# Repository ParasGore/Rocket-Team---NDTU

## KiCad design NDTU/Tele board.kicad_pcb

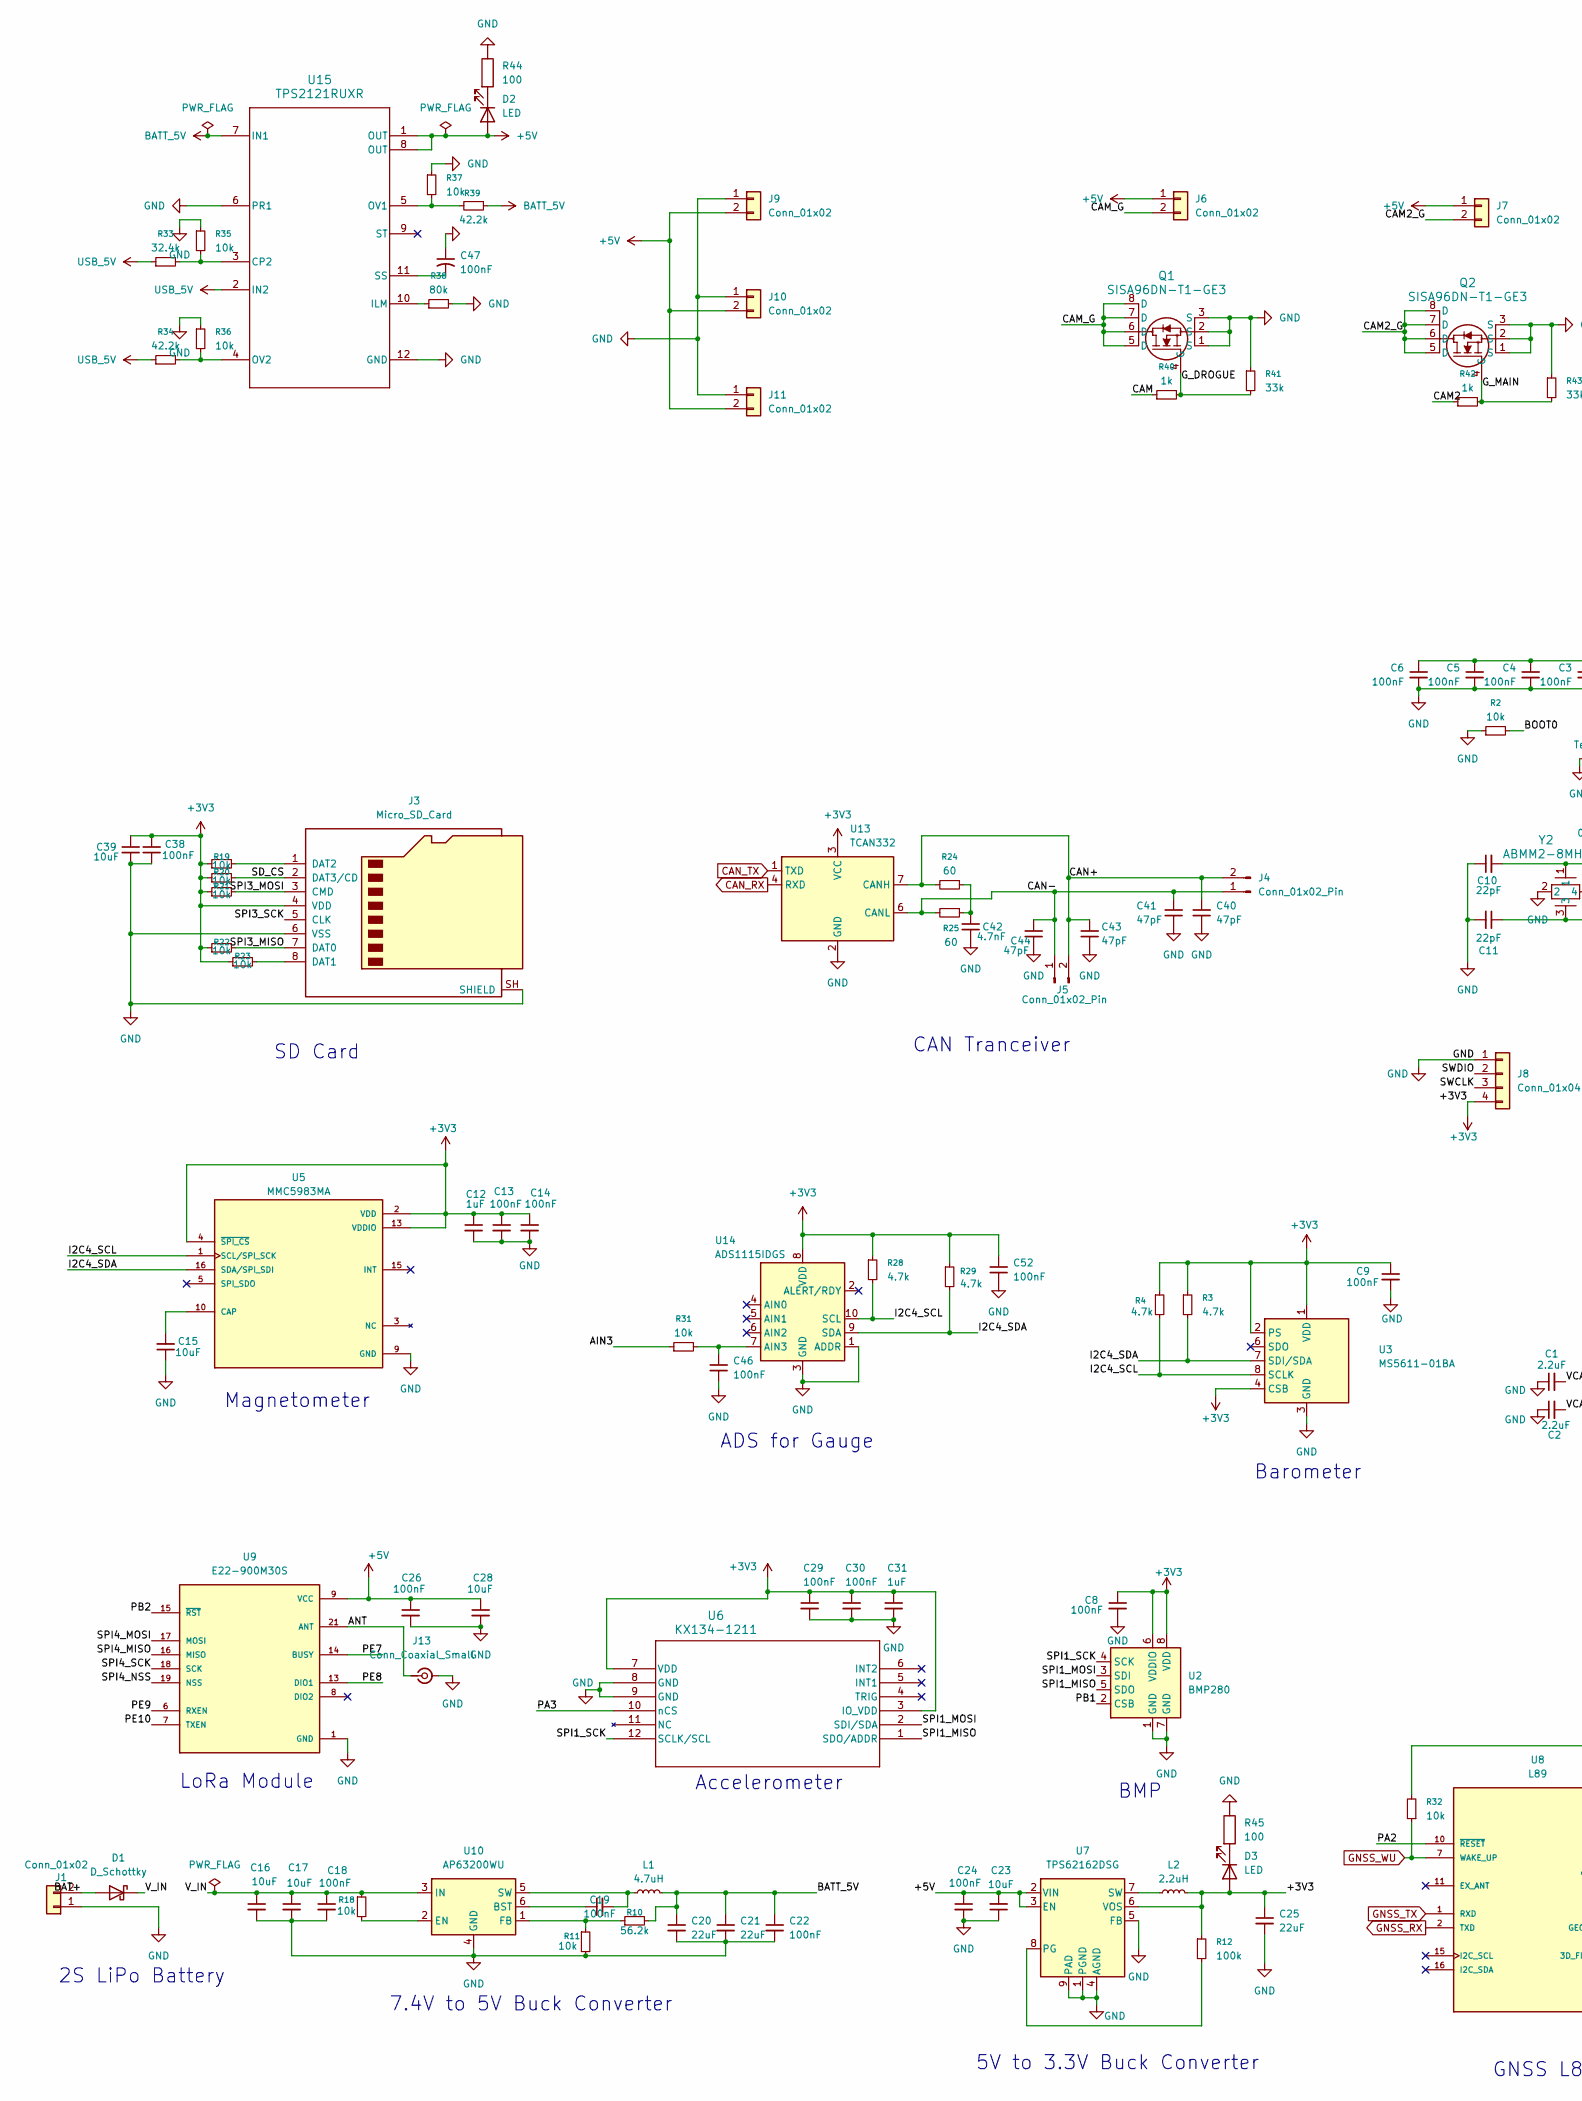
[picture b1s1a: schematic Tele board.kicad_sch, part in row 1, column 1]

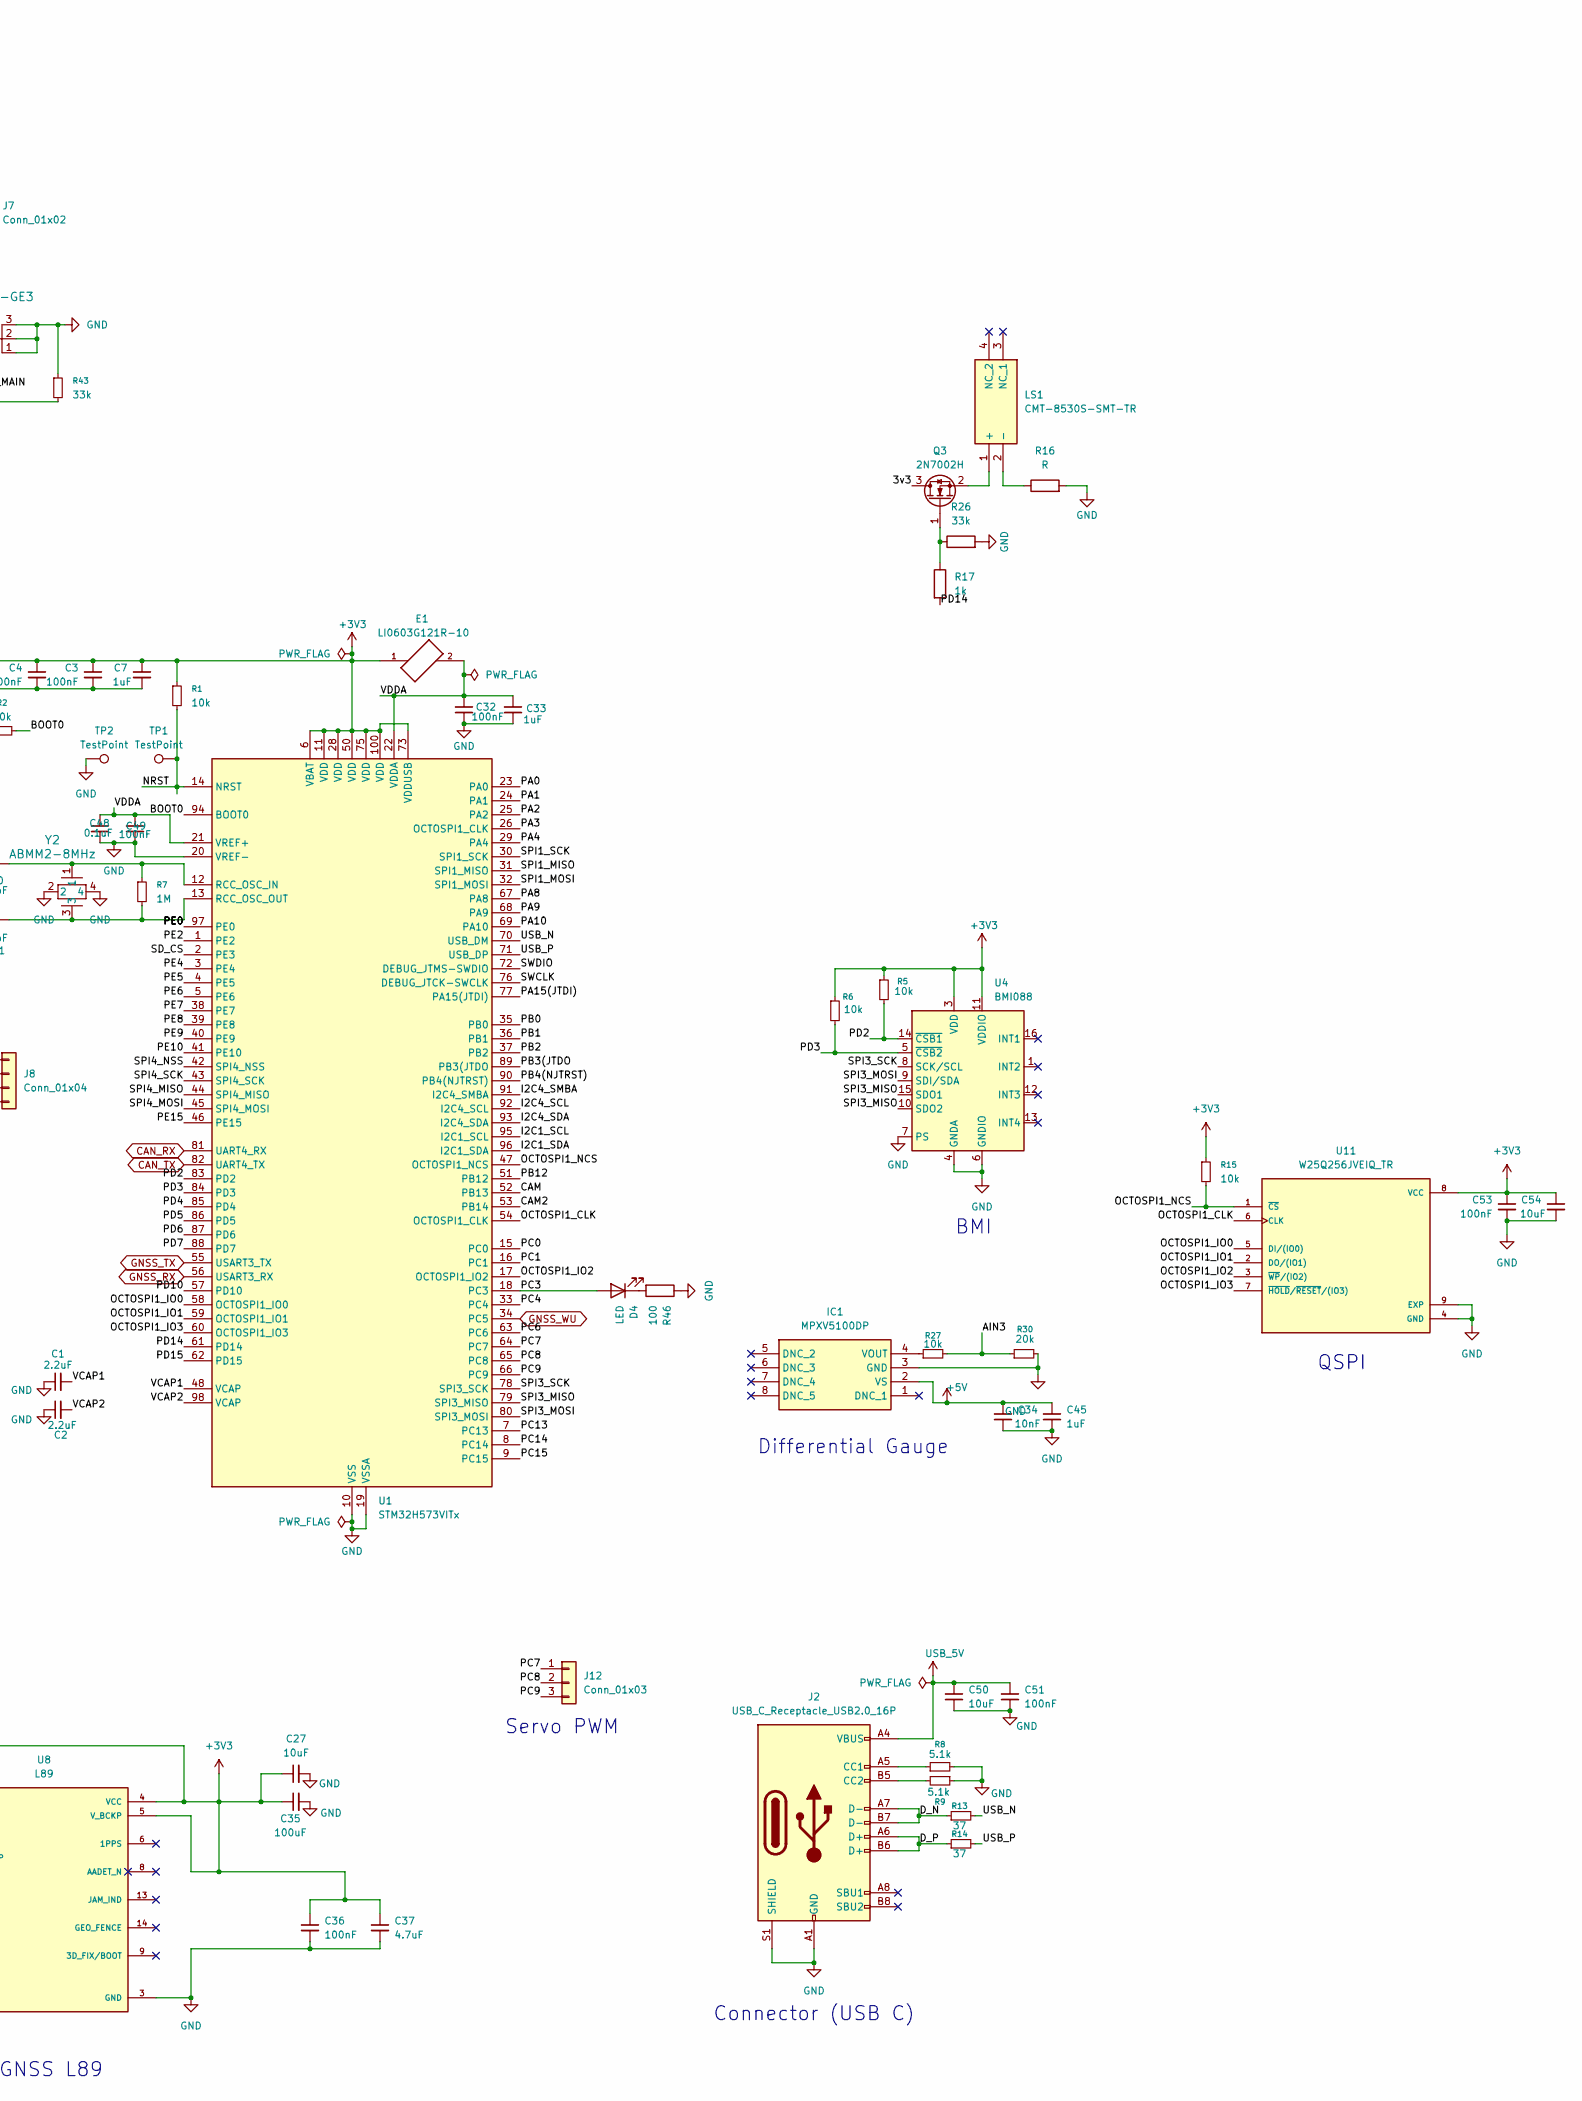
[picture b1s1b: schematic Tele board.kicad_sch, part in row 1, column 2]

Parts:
C1, C2: 2.2uF; C_0603_1608Metric
C3, C4, C5, C6, C8, C9, C13, C14, C18, C19, C22, C24, C26, C29, C30, C32, C36, C38, C46, C47, C49, C51, C52, C53: 100nF; C_0603_1608Metric
C7, C12, C31, C33, C45: 1uF; C_0603_1608Metric
C10, C11: 22pF; C_0603_1608Metric
C15, C16, C17, C23, C27, C28, C39, C50, C54: 10uF; C_0603_1608Metric
C20, C21, C25: 22uF; C_0603_1608Metric
C34: 10nF; C_0603_1608Metric
C35: 100uF; C_0603_1608Metric
C37: 4.7uF; C_0603_1608Metric
C40, C41, C43, C44: 47pF; C_0603_1608Metric
C42: 4.7nF; C_0603_1608Metric
C48: 0.1uF; C_0603_1608Metric
D1: D_Schottky; D_SOD-128
D2, D3, D4: LED; LED_0603_1608Metric
E1: LI0603G121R-10; IND_LI0603G121R-10_LRD-M; PARTREV C
IC1: MPXV5100DP; Manufacturer_Part_Number MPXV5100DP
J1: Conn_01x02; AMASS_XT30U-M_1x02_P5.0mm_Vertical
J2: USB_C_Receptacle_USB2.0_16P; USB_C_Receptacle_GCT_USB4105-xx-A_16P_TopMnt_Horizontal
J3: Micro_SD_Card; microSD_HC_Hirose_DM3AT-SF-PEJM5
J4, J5: Conn_01x02_Pin; JST_EH_B2B-EH-A_1x02_P2.50mm_Vertical
J6, J7, J9, J10, J11: Conn_01x02; JST_EH_B2B-EH-A_1x02_P2.50mm_Vertical
J8: Conn_01x04; JST_EH_B4B-EH-A_1x04_P2.50mm_Vertical
J12: Conn_01x03; AMASS_MR30PW-M_1x03_P3.50mm_Horizontal
J13: Conn_Coaxial_Small; SMA_Samtec_SMA-J-P-H-ST-EM1_EdgeMount
L1: 4.7uH; L_Coilcraft_XAL4020-XXX
L2: 2.2uH; L_Coilcraft_XAL4020-XXX
LS1: CMT-8530S-SMT-TR; CMT8530SSMTTR; Manufacturer_Part_Number CMT-8530S-SMT-TR; Mouser Part Number 490-CMT-8530S-SMT-TR
Q1, Q2: SISA96DN-T1-GE3; SIS862DNT1GE3
Q3: 2N7002H; SOT-23
R1, R2, R5, R6, R11, R15, R18, R19, R20, R21, R22, R23, R27, R31, R32, R35, R36, R37: 10k; R_0603_1608Metric
R3, R4, R28, R29: 4.7k; R_0603_1608Metric
R7: 1M; R_0603_1608Metric
R8, R9: 5.1k; R_0603_1608Metric
R10: 56.2k; R_0603_1608Metric
R12: 100k; R_0603_1608Metric
R13, R14: 37; R_0603_1608Metric
R16: R; R_0603_1608Metric
R17, R40, R42: 1k; R_0603_1608Metric
R24, R25: 60; R_0603_1608Metric
R26, R41, R43: 33k; R_0603_1608Metric
R30: 20k; R_0603_1608Metric
R33: 32.4k; R_0603_1608Metric
R34, R39: 42.2k; R_0603_1608Metric
R38: 80k; R_0603_1608Metric
R44, R45, R46: 100; R_0603_1608Metric
TP1, TP2: TestPoint; TestPoint_Pad_2.0x2.0mm
U1: STM32H573VITx; LQFP-100_14x14mm_P0.5mm
U2: BMP280; Bosch_LGA-8_2x2.5mm_P0.65mm_ClockwisePinNumbering
U3: MS5611-01BA; LGA-8_3x5mm_P1.25mm
U4: BMI088; Bosch_LGA-16_4.5x3mm_P0.5mm_LayoutBorder7x1y_ClockwisePinNu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
U5: MMC5983MA; PQFN50P300X300X100-16N; PARTREV A
U6: KX134-1211; LGA12_2X2X0P9_ROM-M
U7: TPS62162DSG; Texas_DSG0008A_WSON-8-1EP_2x2mm_P0.5mm_EP0.9x1.6mm_ThermalV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
U8: L89; XCVR_L89; PARTREV 1.1
U9: E22-900M30S; XCVR_E22-900M30S; PARTREV 1.2
U10: AP63200WU; TSOT-23-6
U11: W25Q256JVEIQ_TR; W25Q256JVEIQ; MPN W25Q256JVEIQ TR
U13: TCAN332; SOIC-8_3.9x4.9mm_P1.27mm
U14: ADS1115IDGS; TSSOP-10_3x3mm_P0.5mm
U15: TPS2121RUXR; IC_TPS2121RUXR
Y2: ABMM2-8MHz; CRYSTAL_ABMM2_ABR

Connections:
+3V3: C3.1, C4.1, C5.1, C6.1, C7.1, C8.1, C9.1, C12.1, C13.1, C14.1, C25.1, C27.1, C29.1, C30.1, C31.1, C35.1, C36.1, C37.1, C38.1, C39.1, C52.1, C53.1, C54.1, D3.2 (A), E1.1, J3.4 (VDD), J8.4, L2.2, R1.1, R3.1, R4.1, R5.1, R6.1, R12.1, R15.1, R19.1, R20.1, R21.1, R22.1, R23.1, R28.1, R29.1, R32.2, U1.6 (VBAT), U1.11 (VDD), U1.28 (VDD), U1.50 (VDD), U1.73 (VDDUSB), U1.75 (VDD), U1.100 (VDD), U2.6 (VDDIO), U2.8 (VDD), U3.1 (VDD), U3.2 (PS), U3.4 (CSB), U3.5 (CSB), U4.3 (VDD), U4.11 (VDDIO), U5.2 (VDD), U5.4 (~SPI_CS), U5.13 (VDDIO), U6.3 (IO_VDD), U6.7 (VDD), U7.6 (VOS), U8.4 (VCC), U8.5 (V_BCKP), U11.8 (VCC), U13.3 (VCC), U14.8 (VDD)
+5V: C23.2, C24.1, C26.1, C28.1, C34.1, C45.1, D2.2 (A), IC1.2 (VS), J6.1, J7.1, J9.2, J10.2, J11.2, U7.2 (VIN), U7.3 (EN), U9.9 (VCC), U9.10 (VCC), U15.1 (OUT), U15.8 (OUT)
/3v3: Q3.3 (D)
/AIN3: R27.2, R30.1, R31.1
/ANT: J13.1 (In), U9.21 (ANT)
/BAT+: D1.2 (A), J1.2
/BOOT0: R2.2, U1.94 (BOOT0)
/CAM: R40.1, U1.52 (PB13)
/CAM2: R42.1, U1.53 (PB14)
/CAM2_G: J7.2, Q2.5 (D), Q2.6 (D), Q2.7 (D), Q2.8 (D)
/CAM_G: J6.2, Q1.5 (D), Q1.6 (D), Q1.7 (D), Q1.8 (D)
/CAN+: C40.1, C43.1, J4.2, J5.2, R24.2, U13.7 (CANH); also elsewhere on the board
/CAN-: C41.1, C44.1, J4.1, J5.1, R25.2, U13.6 (CANL); also elsewhere on the board
/D_N: J2.A7 (D-), J2.B7 (D-), R13.1
/D_P: J2.A6 (D+), J2.B6 (D+), R14.1
/G_DROGUE: Q1.4 (G), R40.2, R41.2
/G_MAIN: Q2.4 (G), R42.2, R43.2
/I2C1_SCL: U1.95 (I2C1_SCL)
/I2C1_SDA: U1.96 (I2C1_SDA)
/I2C4_SCL: R4.2, R28.2, U1.92 (I2C4_SCL), U3.8 (SCLK), U5.1 (SCL/SPI_SCK), U14.10 (SCL)
/I2C4_SDA: R3.2, R29.2, U1.93 (I2C4_SDA), U3.7 (SDI/SDA), U5.16 (SDA/SPI_SDI), U14.9 (SDA)
/I2C4_SMBA: U1.91 (I2C4_SMBA)
/NRST: R1.2, TP1.1 (1_1), U1.14 (NRST)
/OCTOSPI1_CLK: U1.54 (OCTOSPI1_CLK), U11.6 (CLK)
/OCTOSPI1_IO0: U1.58 (OCTOSPI1_IO0), U11.5 (DI/(IO0))
/OCTOSPI1_IO1: U1.59 (OCTOSPI1_IO1), U11.2 (DO/(IO1))
/OCTOSPI1_IO2: U1.17 (OCTOSPI1_IO2), U11.3 (~WP/(IO2))
/OCTOSPI1_IO3: U1.60 (OCTOSPI1_IO3), U11.7 (~HOLD/~RESET/(IO3))
/OCTOSPI1_NCS: R15.2, U1.47 (OCTOSPI1_NCS), U11.1 (~CS)
/PA0: U1.23 (PA0)
/PA1: U1.24 (PA1)
/PA2: U1.25 (PA2), U8.10 (~RESET)
/PA3: U1.26 (OCTOSPI1_CLK), U6.10 (nCS)
/PA4: U1.29 (PA4)
/PA8: U1.67 (PA8)
/PA9: U1.68 (PA9)
/PA10: U1.69 (PA10)
/PA15(JTDI): U1.77 (PA15(JTDI))
/PB0: U1.35 (PB0)
/PB1: U1.36 (PB1), U2.2 (CSB)
/PB2: U1.37 (PB2), U9.15 (~RST)
/PB3(JTDO: U1.89 (PB3(JTDO)
/PB4(NJTRST): U1.90 (PB4(NJTRST))
/PB12: U1.51 (PB12)
/PC0: U1.15 (PC0)
/PC1: U1.16 (PC1)
/PC3: D4.2 (A), U1.18 (PC3)
/PC4: U1.33 (PC4)
/PC6: U1.63 (PC6)
/PC7: J12.1, U1.64 (PC7)
/PC8: J12.2, U1.65 (PC8)
/PC9: J12.3, U1.66 (PC9)
/PC13: U1.7 (PC13)
/PC14: U1.8 (PC14)
/PC15: U1.9 (PC15)
/PD2: R5.2, U1.83 (PD2), U4.14 (~CSB1)
/PD3: R6.2, U1.84 (PD3), U4.5 (~CSB2)
/PD4: U1.85 (PD4)
/PD5: U1.86 (PD5)
/PD6: U1.87 (PD6)
/PD7: U1.88 (PD7)
/PD10: U1.57 (PD10)
/PD14: R17.2, U1.61 (PD14)
/PD15: U1.62 (PD15)
/PE0: U1.97 (PE0)
/PE2: U1.1 (PE2)
/PE4: U1.3 (PE4)
/PE5: U1.4 (PE5)
/PE6: U1.5 (PE6)
/PE7: U1.38 (PE7), U9.14 (BUSY)
/PE8: U1.39 (PE8), U9.13 (DIO1)
/PE9: U1.40 (PE9), U9.6 (RXEN)
/PE10: U1.41 (PE10), U9.7 (TXEN)
/PE15: U1.46 (PE15)
/SD_CS: J3.2 (DAT3/CD), R20.2, U1.2 (PE3)
/SPI1_MISO: U1.31 (SPI1_MISO), U2.5 (SDO), U6.1 (SDO/ADDR)
/SPI1_MOSI: U1.32 (SPI1_MOSI), U2.3 (SDI), U6.2 (SDI/SDA)
/SPI1_SCK: U1.30 (SPI1_SCK), U2.4 (SCK), U6.12 (SCLK/SCL)
/SPI3_MISO: J3.7 (DAT0), R22.2, U1.79 (SPI3_MISO), U4.10 (SDO2), U4.15 (SDO1)
/SPI3_MOSI: J3.3 (CMD), R21.2, U1.80 (SPI3_MOSI), U4.9 (SDI/SDA)
/SPI3_SCK: J3.5 (CLK), U1.78 (SPI3_SCK), U4.8 (SCK/SCL)
/SPI4_MISO: U1.44 (SPI4_MISO), U9.16 (MISO)
/SPI4_MOSI: U1.45 (SPI4_MOSI), U9.17 (MOSI)
/SPI4_NSS: U1.42 (SPI4_NSS), U9.19 (NSS)
/SPI4_SCK: U1.43 (SPI4_SCK), U9.18 (SCK)
/SWCLK: J8.3, U1.76 (DEBUG_JTCK-SWCLK)
/SWDIO: J8.2, U1.72 (DEBUG_JTMS-SWDIO)
/USB_N: R13.2, U1.70 (USB_DM)
/USB_P: R14.2, U1.71 (USB_DP)
/VCAP1: C1.2, U1.48 (VCAP)
/VCAP2: C2.2, U1.98 (VCAP)
/VDDA: C32.1, C33.1, C48.1, C49.1, E1.2, U1.21 (VREF+), U1.22 (VDDA)
/V_IN: C16.1, C17.1, C18.1, D1.1 (K), R18.1, U10.3 (IN)
BATT_5V: C20.1, C21.1, C22.1, L1.2, R10.2, R39.1, U15.7 (IN1)
CAN_RX: U1.81 (UART4_RX), U13.4 (RXD)
CAN_TX: U1.82 (UART4_TX), U13.1 (TXD)
GND: C1.1, C2.1, C3.2, C4.2, C5.2, C6.2, C7.2, C8.2, C9.2, C10.1, C11.2, C12.2, C13.2, C14.2, C15.1, C16.2, C17.2, C18.2, C20.2, C21.2, C22.2, C23.1, C24.2, C25.2, C26.2, C27.2, C28.2, C29.2, C30.2, C31.2, C32.2, C33.2, C34.2, C35.2, C36.2, C37.2, C38.2, C39.2, C40.2, C41.2, C42.2, C43.2, C44.2, C45.2, C46.2, C47.1, C48.2, C49.2, C50.2, C51.2, C52.2, C53.2, C54.2, IC1.3 (GND), J1.1, J2.A1 (GND), J2.A12 (GND), J2.B1 (GND), J2.B12 (GND), J2.S1 (SHIELD), J3.6 (VSS), J3.SH (SHIELD), J8.1, J9.1, J10.1, J11.1, J13.2 (Ext), Q1.1 (S), Q1.2 (S), Q1.3 (S), Q2.1 (S), Q2.2 (S), Q2.3 (S), R2.1, R8.2, R9.1, R11.2, R16.2, R26.2, R30.2, R35.1, R36.1, R37.1, R38.2, R41.1, R43.1, R44.1, R45.1, R46.1, TP2.1 (1_1), U1.10 (VSS), U1.19 (VSSA), U1.20 (VREF-), U1.27 (VSS), U1.49 (VSS), U1.74 (VSS), U1.99 (VSS), U2.1 (GND), U2.7 (GND), U3.3 (GND), U4.2 (GNDA), U4.4 (GNDA), U4.6 (GNDIO), U4.7 (PS), U5.9 (GND), U5.11 (GND), U6.8 (GND), U6.9 (GND), U7.1 (PGND), U7.4 (AGND), U7.5 (FB), U7.9 (PAD), U8.3 (GND), U8.12 (GND), U9.1 (GND), U9.2 (GND), U9.3 (GND), U9.4 (GND), U9.5 (GND), U9.11 (GND), U9.12 (GND), U9.20 (GND), U9.22 (GND), U10.4 (GND), U11.4 (GND), U11.9 (EXP), U13.2 (GND), U14.1 (ADDR), U14.3 (GND), U15.6 (PR1), U15.12 (GND), Y2.2, Y2.4; also elsewhere on the board
GNSS_RX: U1.56 (USART3_RX), U8.2 (TXD)
GNSS_TX: U1.55 (USART3_TX), U8.1 (RXD)
GNSS_WU: R32.1, U1.34 (PC5), U8.7 (WAKE_UP)
unnamed: C42.1, R24.1, R25.1
unnamed: D2.1 (K), R44.2
unnamed: D3.1 (K), R45.2
unnamed: D4.1 (K), R46.2
unnamed: IC1.4 (VOUT), R27.1
unnamed: J2.A5 (CC1), R8.1
unnamed: J2.B5 (CC2), R9.2
unnamed: J3.8 (DAT1), R23.2
unnamed: J3.1 (DAT2), R19.2
unnamed: LS1.1 (+), Q3.2 (S)
unnamed: LS1.2 (-), R16.1
unnamed: Q3.1 (G), R17.1, R26.1
unnamed: C10.2, R7.1, U1.12 (RCC_OSC_IN), Y2.1
unnamed: C11.1, R7.2, U1.13 (RCC_OSC_OUT), Y2.3
unnamed: C15.2, U5.10 (CAP)
unnamed: R12.2, U7.8 (PG)
unnamed: L2.1, U7.7 (SW)
unnamed: C19.1, U10.6 (BST)
unnamed: R18.2, U10.2 (EN)
unnamed: R10.1, R11.1, U10.1 (FB)
unnamed: C19.2, L1.1, U10.5 (SW)
unnamed: C46.1, R31.2, U14.7 (AIN3)
unnamed: R33.2, R35.2, U15.3 (CP2)
unnamed: R38.1, U15.10 (ILM)
unnamed: R37.2, R39.2, U15.5 (OV1)
unnamed: R34.2, R36.2, U15.4 (OV2)
unnamed: C47.2, U15.11 (SS)
USB_5V: C50.1, C51.1, J2.A4 (VBUS), J2.A9 (VBUS), J2.B4 (VBUS), J2.B9 (VBUS), R33.1, R34.1, U15.2 (IN2)

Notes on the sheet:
ADS for Gauge
GNSS L89
5V to 3.3V Buck Converter
QSPI
Connector (USB C)
Barometer
Magnetometer
BMI
BMP
2S LiPo Battery
SD Card
Differential Gauge
CAN Tranceiver
Servo PWM
Accelerometer
LoRa Module
7.4V to 5V Buck Converter

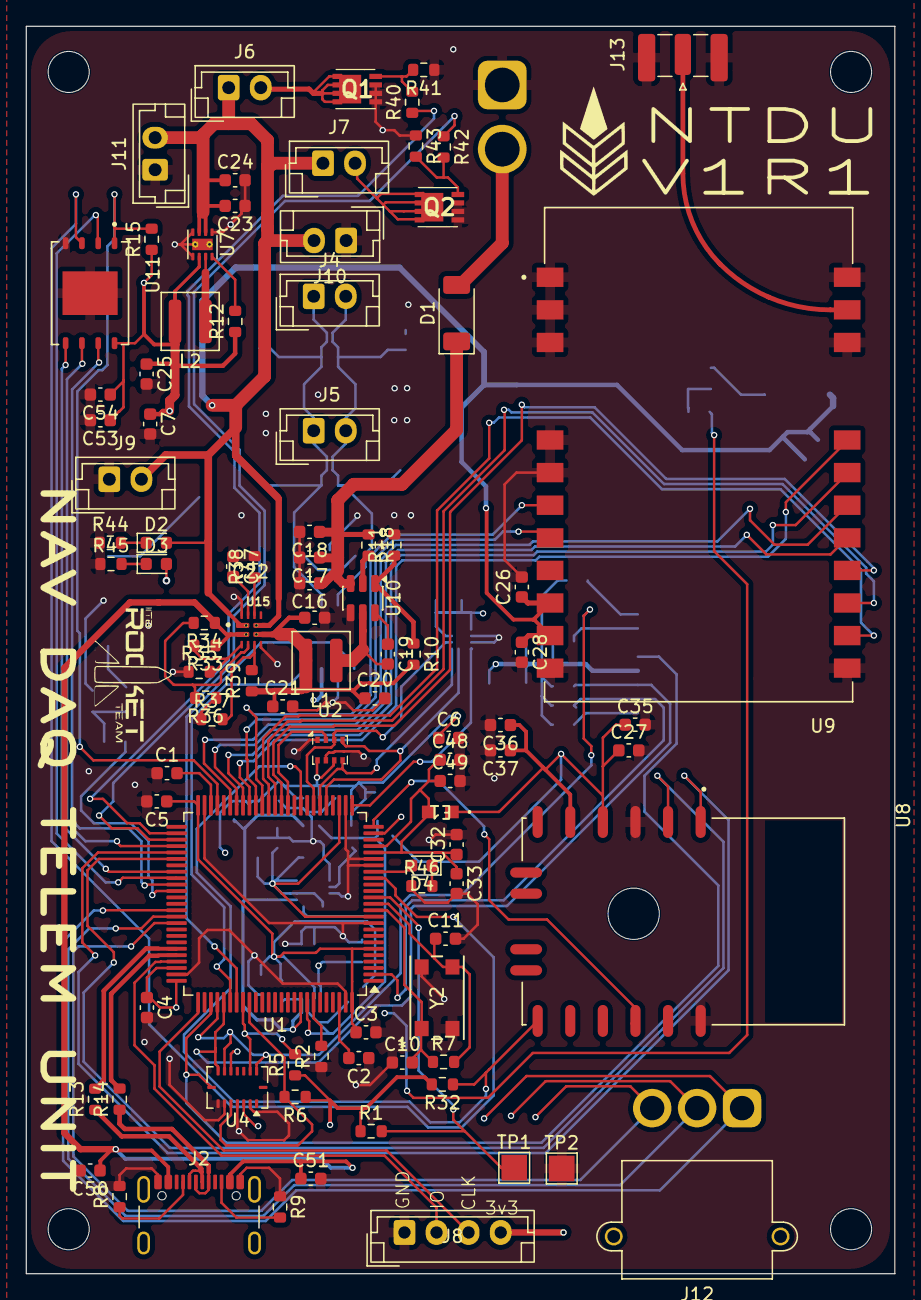
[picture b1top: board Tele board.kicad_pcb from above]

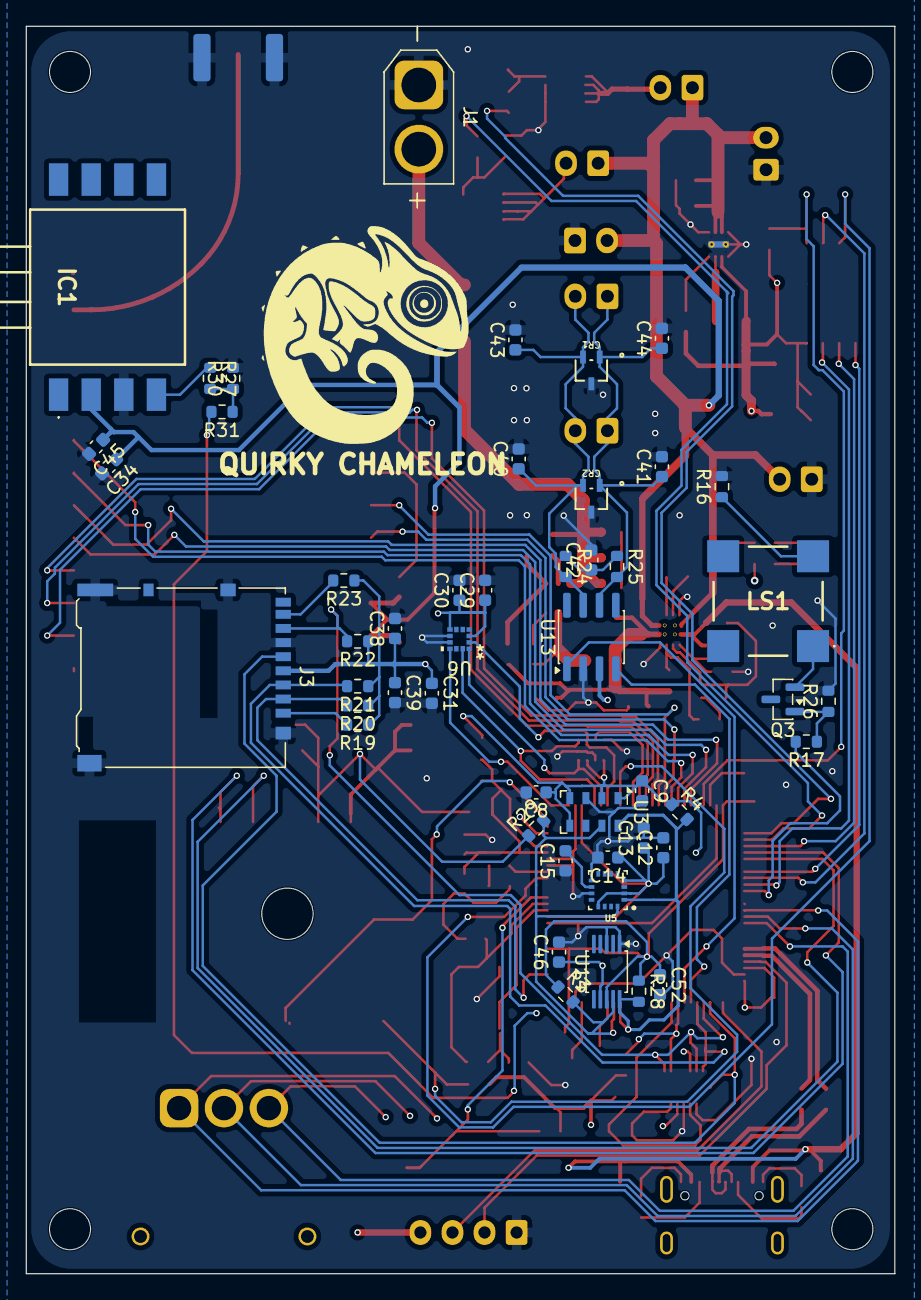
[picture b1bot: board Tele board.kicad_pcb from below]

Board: 4 copper layers, 67.7 x 97.2 mm, 144 parts (49 on the bottom side), 94 nets.

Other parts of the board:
CR1, CR2: ESDCAN02-2BWY; SOT323-3L_STM

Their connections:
/CAN+: CR1.2, CR2.2; also elsewhere on the board
/CAN-: CR1.1, CR2.1; also elsewhere on the board
GND: CR1.3, CR2.3; also elsewhere on the board
